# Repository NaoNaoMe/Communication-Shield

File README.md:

Communication Shield
=========

The Communication Shield is designed as easy to connect to the uart pins.
This shield adapts with any dev board that has an Arduino standard footprint.

Repository Contents
-------------------
* **/Hardware** - All Eagle design files (.brd, .sch)
* **/Cables** - Cables info

Description(Pin Interfaces)
-------------------

### CN1 Pin Descriptions:
| Pin | Name  | Description                                       |
| --- | ----- | ------------------------------------------------- |
| 1   | IOREF | It depends on your board voltage reference        |
| 2   | TX    | It connects to the IOL-0pin                       |
| 3   | RX    | It connects to the IOL-1pin                       |
| 4   | GND   | GND                                               |
| 5   | -     | No connection.                                    |

License
-------------------
The repository is released under [Creative Commons ShareAlike 4.0 International](https://creativecommons.org/licenses/by-sa/4.0/).

Distributed as-is; no warranty is given.

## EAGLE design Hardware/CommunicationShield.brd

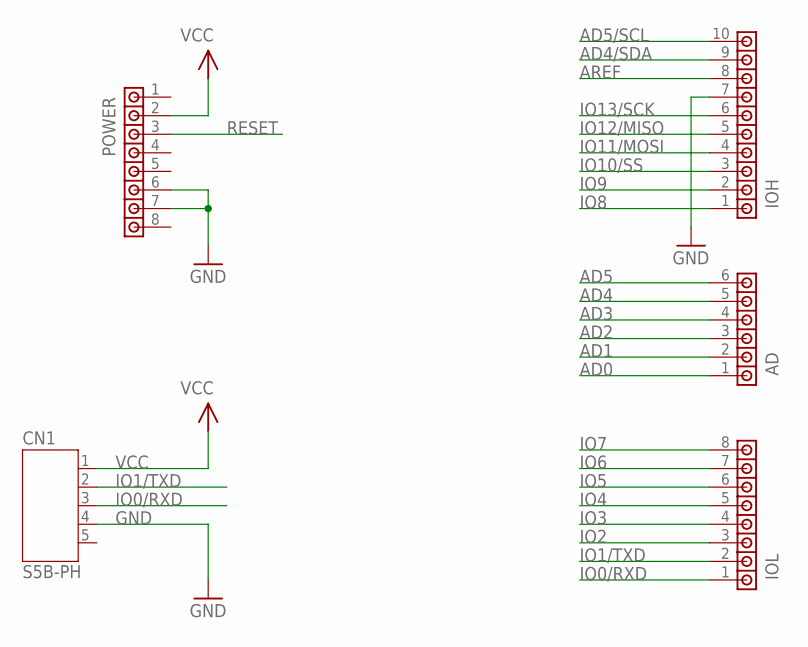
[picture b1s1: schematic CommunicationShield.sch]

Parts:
AD: PINHD-1X6
CN1: S5B-PH
IOH: PINHD-1X10
IOL: PINHD-1X8
POWER: PINHD-1X8

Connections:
AD0: AD.1
AD1: AD.2
AD2: AD.3
AD3: AD.4
AD4: AD.5
AD4/SDA: IOH.9
AD5: AD.6
AD5/SCL: IOH.10
AREF: IOH.8
GND: CN1.4, IOH.7, POWER.6, POWER.7
IO0/RXD: CN1.3, IOL.1
IO1/TXD: CN1.2, IOL.2
IO2: IOL.3
IO3: IOL.4
IO4: IOL.5
IO5: IOL.6
IO6: IOL.7
IO7: IOL.8
IO8: IOH.1
IO9: IOH.2
IO10/SS: IOH.3
IO11/MOSI: IOH.4
IO12/MISO: IOH.5
IO13/SCK: IOH.6
RESET: POWER.3
VCC: CN1.1, POWER.2

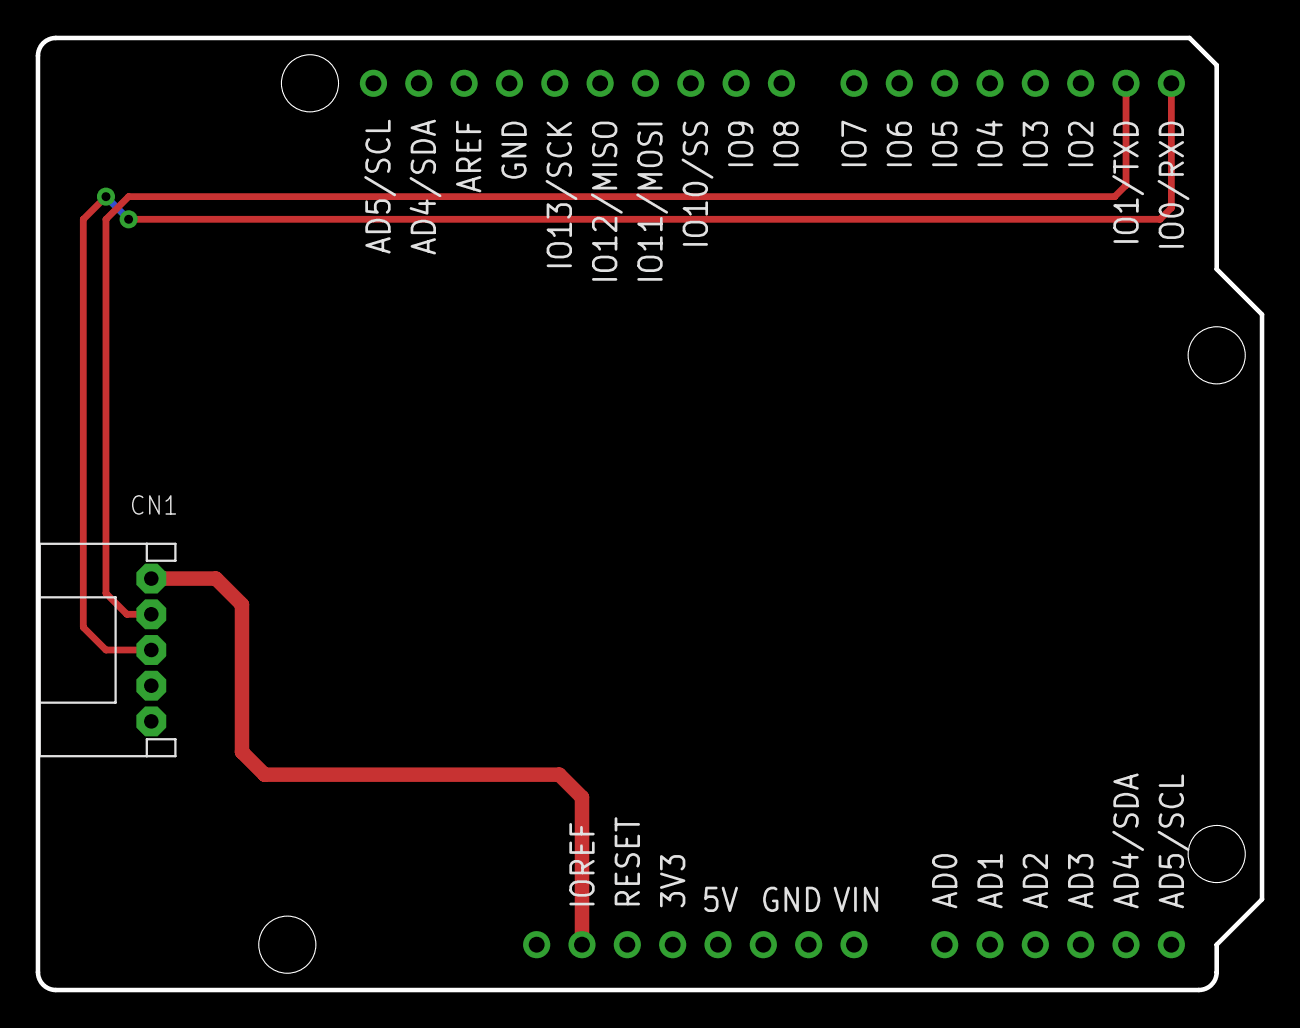
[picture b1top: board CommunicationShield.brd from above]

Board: 2 copper layers, 68.6 x 53.3 mm, 5 parts (0 on the bottom side), 4 nets.

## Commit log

2018-04-18 Upload files
2018-04-18 Fix cables info

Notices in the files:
parts and their libraries:
jst: Copyright (C) 2016, Naoya Imai
